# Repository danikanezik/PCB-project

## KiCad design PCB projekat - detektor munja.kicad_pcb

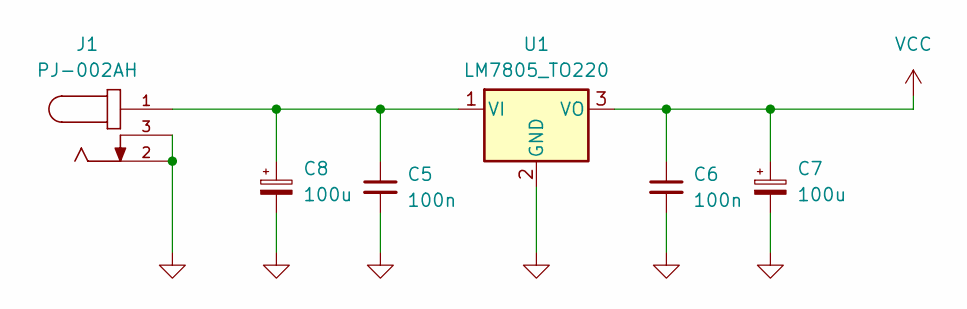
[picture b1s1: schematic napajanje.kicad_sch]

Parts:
C5, C6: 100n; C_Disc_D3.0mm_W1.6mm_P2.50mm
C7, C8: 100u; C_Radial_D4.0mm_H5.0mm_P1.50mm
J1: PJ-002AH; CUI_PJ-002AH
U1: LM7805_TO220; TO-220-3_Vertical

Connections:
GND: C5.2, C6.2, C7.2, C8.2, J1.2, J1.3, U1.2 (GND); also elsewhere on the board
unnamed: C5.1, C8.1, J1.1, U1.1 (VI)
VCC: C6.1, C7.1, U1.3 (VO); also elsewhere on the board

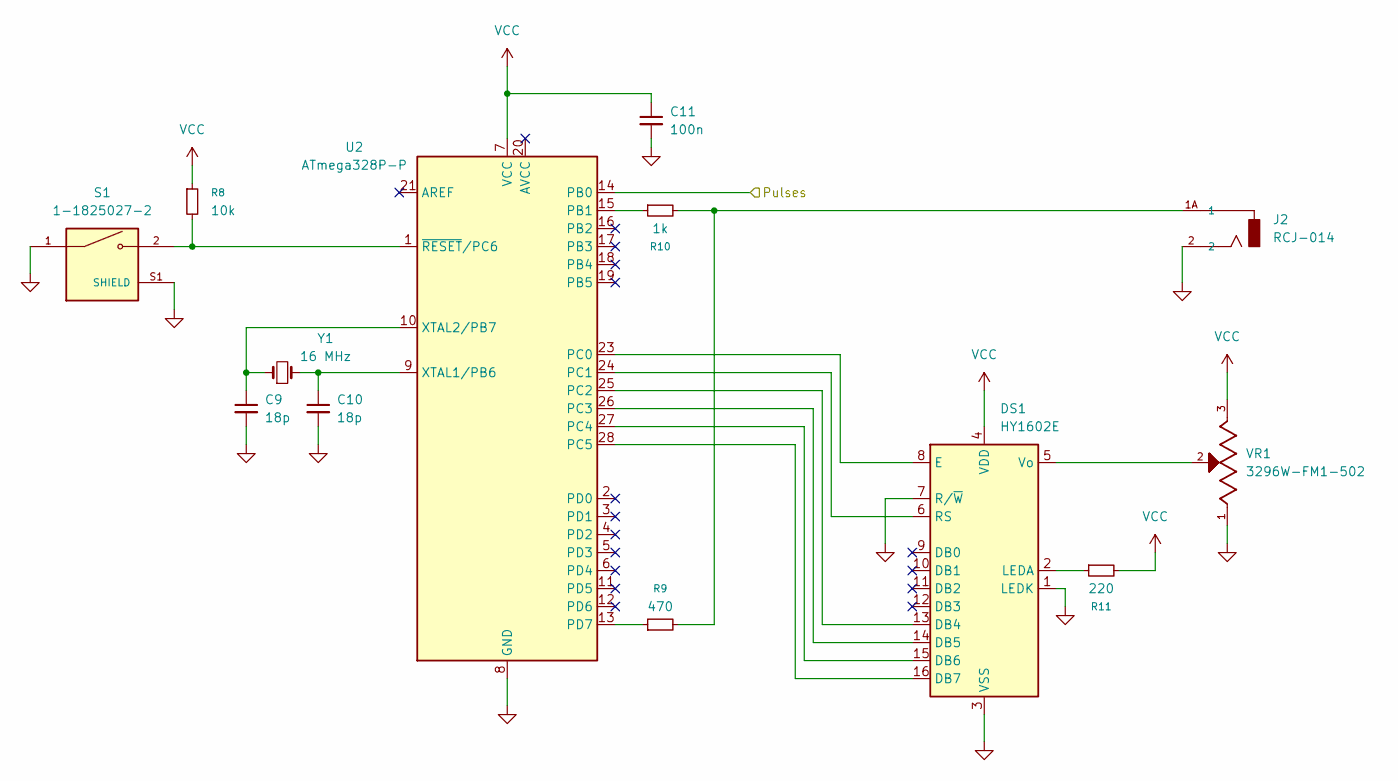
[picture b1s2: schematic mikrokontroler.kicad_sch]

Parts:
C9, C10: 18p; C_Disc_D3.0mm_W1.6mm_P2.50mm
C11: 100n; C_Disc_D3.0mm_W1.6mm_P2.50mm
DS1: HY1602E
J2: RCJ-014; CUI_RCJ-014; PART_REV B
R8: 10k; R_Axial_DIN0207_L6.3mm_D2.5mm_P7.62mm_Horizontal
R9: 470; R_Axial_DIN0207_L6.3mm_D2.5mm_P7.62mm_Horizontal
R10: 1k; R_Axial_DIN0207_L6.3mm_D2.5mm_P7.62mm_Horizontal
R11: 220; R_Axial_DIN0207_L6.3mm_D2.5mm_P7.62mm_Horizontal
S1: 1-1825027-2; SW_1-1825027-2; PARTREV G4
U2: ATmega328P-P; DIP-28_W7.62mm
VR1: 3296W-FM1-502; TRIM_3296W-FM1-502; PARTREV 05/16
Y1: 16 MHz; Crystal_HC49-U_Vertical

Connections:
GND: C9.2, C10.2, C11.2, DS1.1 (LEDK), DS1.3 (VSS), DS1.7 (R/~W), J2.2, S1.1, S1.S1 (SHIELD), S1.S2 (SHIELD), U2.8 (GND), U2.22 (GND), VR1.1; also elsewhere on the board
unnamed: DS1.13 (DB4), U2.25 (PC2)
unnamed: DS1.14 (DB5), U2.26 (PC3)
unnamed: DS1.15 (DB6), U2.27 (PC4)
unnamed: DS1.16 (DB7), U2.28 (PC5)
unnamed: DS1.8 (E), U2.23 (PC0)
unnamed: DS1.2 (LEDA), R11.1
unnamed: DS1.6 (RS), U2.24 (PC1)
unnamed: DS1.5 (Vo), VR1.2
unnamed: J2.1A (1), J2.1B (1), J2.1C (1), R9.2, R10.2
unnamed: R10.1, U2.15 (PB1)
unnamed: R9.1, U2.13 (PD7)
unnamed: C10.1, U2.9 (XTAL1/PB6), Y1.2
unnamed: C9.1, U2.10 (XTAL2/PB7), Y1.1
unnamed: R8.2, S1.2, U2.1 (~RESET/PC6)
Pulses: U2.14 (PB0); also elsewhere on the board
VCC: C11.1, DS1.4 (VDD), R8.1, R11.2, U2.7 (VCC), VR1.3; also elsewhere on the board

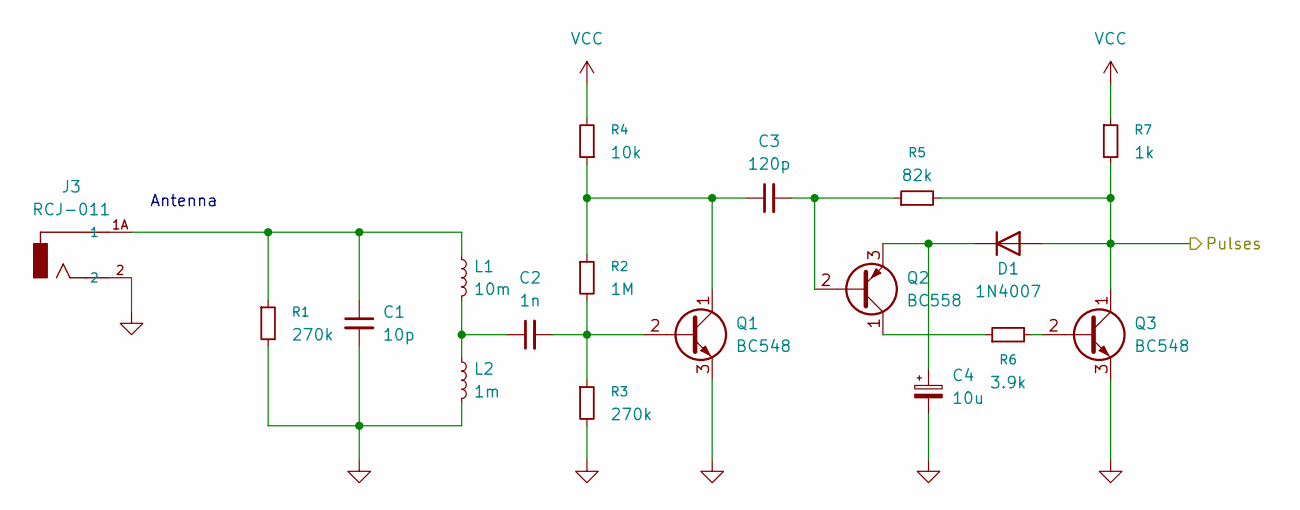
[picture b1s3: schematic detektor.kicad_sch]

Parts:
C1: 10p; C_Disc_D3.0mm_W1.6mm_P2.50mm
C2: 1n; C_Disc_D3.0mm_W1.6mm_P2.50mm
C3: 120p; C_Disc_D3.0mm_W1.6mm_P2.50mm
C4: 10u; C_Radial_D4.0mm_H5.0mm_P1.50mm
D1: 1N4007; D_DO-35_SOD27_P7.62mm_Horizontal
J3: RCJ-011; CUI_RCJ-011; PART_REV B
L1: 10m; L_Radial_L8.0mm_W8.0mm_P5.00mm_Neosid_NE-CPB-07E
L2: 1m; L_Radial_L8.0mm_W8.0mm_P5.00mm_Neosid_NE-CPB-07E
Q1, Q3: BC548; TO-92_Inline
Q2: BC558; TO-92_Inline
R1, R3: 270k; R_Axial_DIN0207_L6.3mm_D2.5mm_P7.62mm_Horizontal
R2: 1M; R_Axial_DIN0207_L6.3mm_D2.5mm_P7.62mm_Horizontal
R4: 10k; R_Axial_DIN0207_L6.3mm_D2.5mm_P7.62mm_Horizontal
R5: 82k; R_Axial_DIN0207_L6.3mm_D2.5mm_P7.62mm_Horizontal
R6: 3.9k; R_Axial_DIN0207_L6.3mm_D2.5mm_P7.62mm_Horizontal
R7: 1k; R_Axial_DIN0207_L6.3mm_D2.5mm_P7.62mm_Horizontal

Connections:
GND: C1.2, C4.2, J3.2, L2.2, Q1.3 (E), Q3.3 (E), R1.2, R3.2; also elsewhere on the board
unnamed: C1.1, J3.1A (1), J3.1B (1), J3.1C (1), L1.1, R1.1
unnamed: C2.1, L1.2, L2.1
unnamed: C4.1, D1.1 (K), Q2.3 (E)
unnamed: C2.2, Q1.2 (B), R2.2, R3.1
unnamed: C3.1, Q1.1 (C), R2.1, R4.1
unnamed: C3.2, Q2.2 (B), R5.1
unnamed: Q2.1 (C), R6.1
unnamed: Q3.2 (B), R6.2
Pulses: D1.2 (A), Q3.1 (C), R5.2, R7.2; also elsewhere on the board
VCC: R4.2, R7.1; also elsewhere on the board

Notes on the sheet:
Antenna

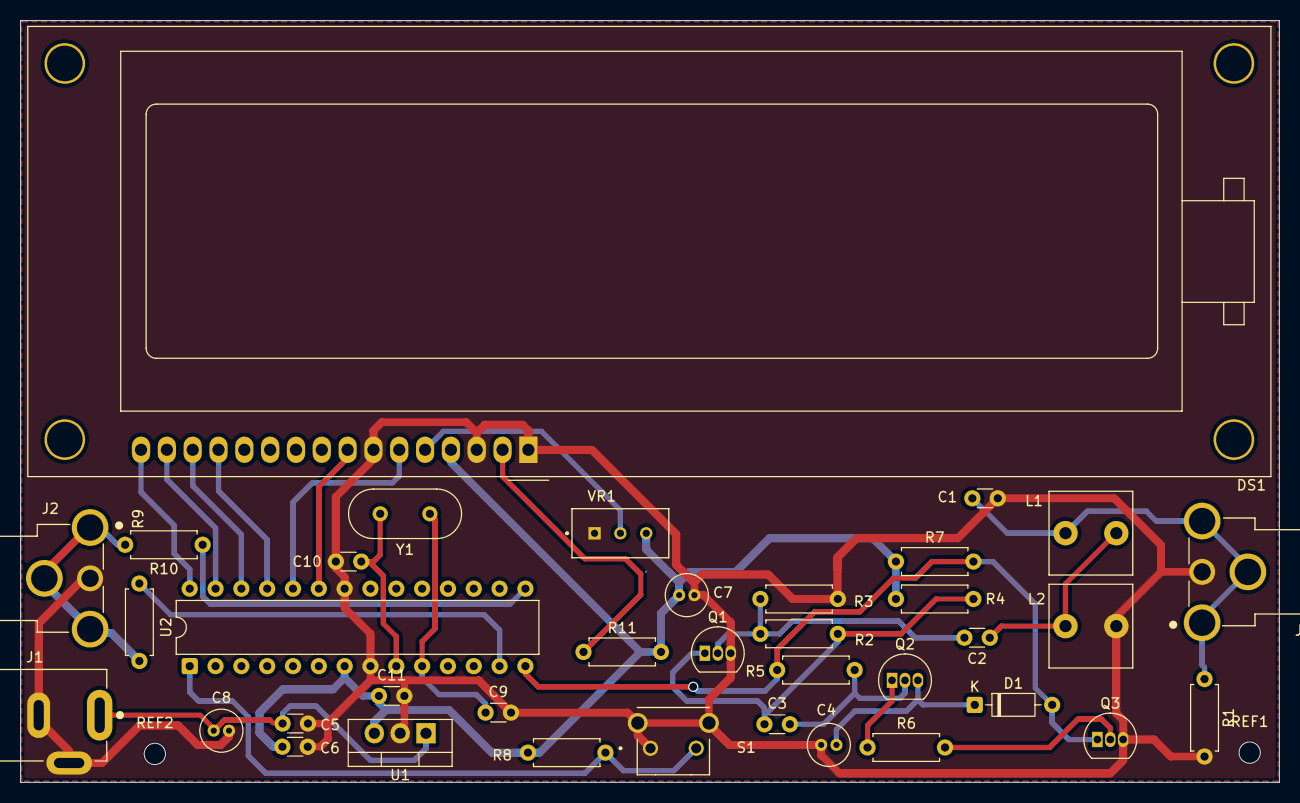
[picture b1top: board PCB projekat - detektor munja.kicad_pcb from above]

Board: 2 copper layers, 123.8 x 74.9 mm, 39 parts (0 on the bottom side), 26 nets.

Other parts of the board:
REF1, REF2: MountingHole_2.1mm
